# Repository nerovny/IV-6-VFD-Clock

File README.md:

# ИВ-6 VFD Digital Clock
+ _board: revision 1.0.0_
+ _firmware: version 0.1 Alpha_
## Overview
This is a basic 6-digit, 7-segment clock based on Soviet ИВ-6 vacuum fluorescent tubes, powered by a widely accessible STM32F103CBT6 microcontroller. 

+ No AI
+ No WiFi
+ USB-C powered

The core concept involves using a single 5V (USB-C) power source and converting the voltage to the 3.3V, 1.2V, and 30–35V levels required to operate the VFD tubes, microcontroller, and logic ICs. 
These circuits can be seen around the location of the rotary encoder on the right side of the board.

The circuit employs sequential updating of CD4511 BCD-to-7-segment latches and static control of the vacuum fluorescent tubes using TBD62783A eight-channel drivers. 
The static function of the VFD eliminates the flickering, extends the life of the lamps, but requires much more ICs.

The unused MCU pins and 5v, 3v3 power rails are accessible via the 2.54mm headers and can be used for an additional LEDs, buttons, logic circuitry etc.

## Hardware
The 110x54mm 4-layer board is tight, but definitely doable by hand with the good iron. The road is mastered by the one who walks it.
+ [Schematic PDF](hardware/schematic.pdf)
+ [Interactive BOM HTML](http://htmlpreview.github.io/?https://github.com/nerovny/IV-6-VFD-Clock/blob/main/hardware/bom/ibom.html)
+ [Board dimensions](hardware/VFD_IV6_dimensions.png)
+ [Fabrication files](hardware/Gerber/)

## Firmware
The latest binary is [HERE](https://github.com/nerovny/IV-6-VFD-Clock/releases)

Use the onboard SWD header and STM32CubeProgrammer to flash it.

The firmware made with VSCode + PlatformIO using some HAL drivers. Source code is provided: just clone the repo and open the project with PIO VSCode plugin.

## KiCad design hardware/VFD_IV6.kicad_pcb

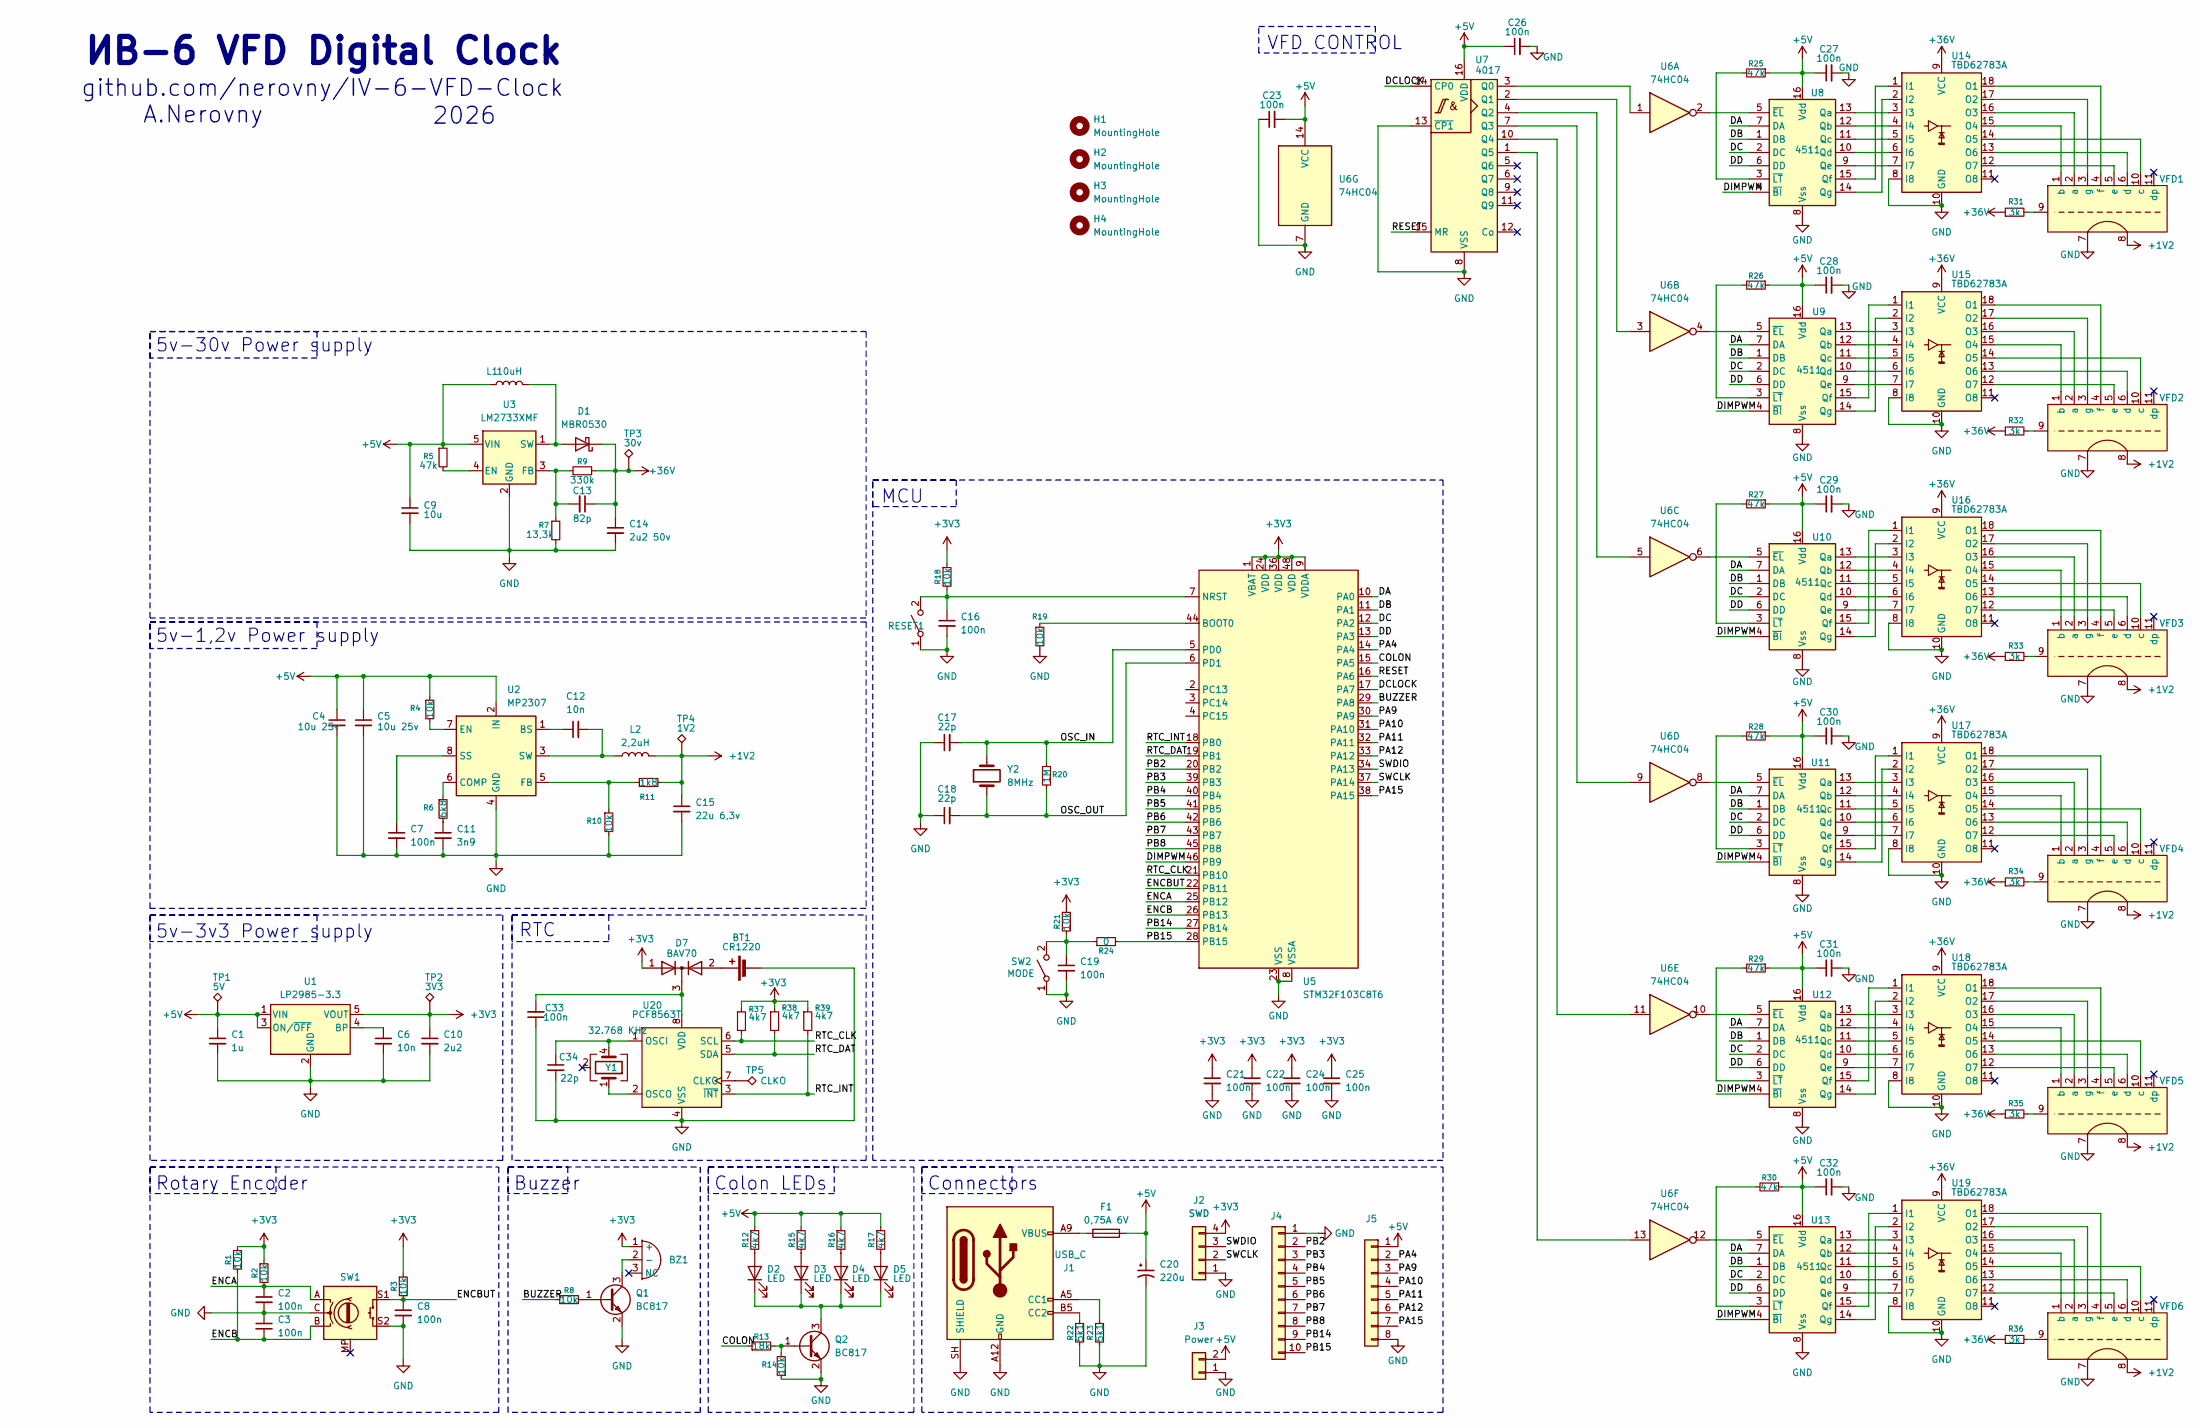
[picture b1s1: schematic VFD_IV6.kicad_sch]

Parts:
BT1: CR1220; RSPRO1220
BZ1: HCT5020
C1: 1u; C_0805_2012Metric
C2, C3, C7, C8, C16, C19, C21, C22, C24, C25, C33: 100n; C_0603_1608Metric
C4, C5: 10u 25v; C_0805_2012Metric
C6, C12: 10n; C_0603_1608Metric
C9: 10u; C_0805_2012Metric
C10: 2u2; C_0805_2012Metric
C11: 3n9; C_0603_1608Metric
C13: 82p; C_0603_1608Metric
C14: 2u2 50v; C_1210_3225Metric
C15: 22u 6,3v; C_1210_3225Metric
C17, C18: 22p; C_0603_1608Metric
C20: 220u; CP_EIA-7360-38_Kemet-E
C23, C26, C27, C28, C29, C30, C31, C32: 100n; C_0805_2012Metric
C34: 22p; C_0402_1005Metric
D1: MBR0530; D_SOD-123
D2, D3, D4, D5: LED; LED_0603_1608Metric
D7: BAV70; SOT-23
F1: 0,75A 6V; Fuse_1210_3225Metric
H1, H2, H3, H4: MountingHole; MountingHole_2.7mm_M2.5_DIN965_Pad
J1: USB_C; USB_C_Receptacle_HRO_TYPE-C-31-M-17
J2: SWD; PinHeader_1x04_P2.54mm_Vertical
J3: Power; JST_XH_B2B-XH-A_1x02_P2.50mm_Vertical
J4: Conn_01x10; PinHeader_1x10_P2.54mm_Vertical
J5: Conn_01x06; PinHeader_1x08_P2.54mm_Vertical
L1: 10uH; L_APV_APH0650
L2: 2,2uH; L_APV_APH0650
Q1, Q2: BC817; SOT-23
R1, R2, R3, R4, R8, R10, R14, R18, R19, R21: 10k; R_0603_1608Metric
R5, R25, R26, R27, R28, R29, R30: 47k; R_0603_1608Metric
R6: 6k8; R_0603_1608Metric
R7: 13,3k; R_0603_1608Metric
R9: 330k; R_0603_1608Metric
R11: 1k8; R_0603_1608Metric
R12, R15, R16, R17: 4k7; R_0603_1608Metric
R13: 18k; R_0603_1608Metric
R20: 1M; R_0603_1608Metric
R22, R23: 5k1; R_0603_1608Metric
R24: 0; R_0603_1608Metric
R31, R32, R33, R34, R35, R36: 3k; R_1206_3216Metric
R37, R38, R39: 4k7; R_0402_1005Metric
RESET1: SW_SPST; SW_SPST_CK_RS282G05A3
SW1: RotaryEncoder_Switch_MP; RotaryEncoder_Alps_EC12E-Switch_Vertical_H20mm
SW2: MODE; SW_Tactile_SPST_Angled_PTS645Vx39-2LFS
TP1: 5V; TestPoint_Pad_1.0x1.0mm
TP2: 3V3; TestPoint_Pad_1.0x1.0mm
TP3: 30v; TestPoint_Pad_1.0x1.0mm
TP4: 1V2; TestPoint_Pad_1.0x1.0mm
TP5: CLKO; TestPoint_Pad_1.0x1.0mm
U1: LP2985-3.3; SOT-23-5
U2: MP2307; SOIC-8_3.9x4.9mm_P1.27mm
U3: LM2733XMF; SOT-23-5
U5: STM32F103C8T6; LQFP-48_7x7mm_P0.5mm
U6: 74HC04; SOIC-14_3.9x8.7mm_P1.27mm
U7: 4017; SOIC-16_3.9x9.9mm_P1.27mm
U8, U9, U10, U11, U12, U13: 4511; SOP-16_4.4x10.4mm_P1.27mm
U14, U15, U16, U17, U18, U19: TBD62783A; SOIC-18W_7.5x11.6mm_P1.27mm
U20: PCF8563T; SOIC-8_3.9x4.9mm_P1.27mm
VFD1, VFD2, VFD3, VFD4, VFD5, VFD6: IV-6_Horizontal
Y1: 32.768 KHz; Crystal_SMD_SeikoEpson_MC306-4Pin_8.0x3.2mm
Y2: 8MHz; Crystal_SMD_5032-2Pin_5.0x3.2mm_HandSoldering

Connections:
+1V2: C15.1, L2.2, R11.2, TP4.1 (1_1), VFD1.8, VFD2.8, VFD3.8, VFD4.8, VFD5.8, VFD6.8
+3V3: BZ1.1 (+), C10.1, C21.1, C22.1, C24.1, C25.1, D7.1 (A), J2.4, R1.1, R2.1, R3.1, R18.1, R21.1, R37.1, R38.1, R39.1, TP2.1 (1_1), U1.5 (VOUT), U5.1 (VBAT), U5.9 (VDDA), U5.24 (VDD), U5.36 (VDD), U5.48 (VDD)
+5V: C1.1, C4.1, C5.1, C9.1, C20.1, C23.2, C26.1, C27.1, C28.1, C29.1, C30.1, C31.1, C32.1, F1.1, J3.2, J5.1, L1.1, R4.1, R5.1, R12.1, R15.1, R16.1, R17.1, R25.1, R26.1, R27.1, R28.1, R29.1, R30.1, TP1.1 (1_1), U1.1 (VIN), U1.3 (ON/~OFF), U2.2 (IN), U3.5 (VIN), U6.14 (VCC), U7.16 (VDD), U8.16 (Vdd), U9.16 (Vdd), U10.16 (Vdd), U11.16 (Vdd), U12.16 (Vdd), U13.16 (Vdd)
+36V: C13.1, C14.1, D1.1 (K), R9.2, R31.1, R32.1, R33.1, R34.1, R35.1, R36.1, TP3.1 (1_1), U14.9 (VCC), U15.9 (VCC), U16.9 (VCC), U17.9 (VCC), U18.9 (VCC), U19.9 (VCC)
/BUZZER: R8.1, U5.29 (PA8)
/COLON: R13.1, U5.15 (PA5)
/DA: U5.10 (PA0), U8.7 (DA), U9.7 (DA), U10.7 (DA), U11.7 (DA), U12.7 (DA), U13.7 (DA)
/DB: U5.11 (PA1), U8.1 (DB), U9.1 (DB), U10.1 (DB), U11.1 (DB), U12.1 (DB), U13.1 (DB)
/DC: U5.12 (PA2), U8.2 (DC), U9.2 (DC), U10.2 (DC), U11.2 (DC), U12.2 (DC), U13.2 (DC)
/DCLOCK: U5.17 (PA7), U7.14 (CP0); also elsewhere on the board
/DD: U5.13 (PA3), U8.6 (DD), U9.6 (DD), U10.6 (DD), U11.6 (DD), U12.6 (DD), U13.6 (DD)
/DIMPWM: U5.46 (PB9), U8.4 (~BI), U9.4 (~BI), U10.4 (~BI), U11.4 (~BI), U12.4 (~BI), U13.4 (~BI)
/ENCA: C2.1, R2.2, SW1.A, U5.25 (PB12)
/ENCB: C3.2, R1.2, SW1.B, U5.26 (PB13)
/ENCBUT: C8.1, R3.2, SW1.S1, U5.22 (PB11)
/OSC_IN: C17.2, R20.1, U5.5 (PD0), Y2.2
/OSC_OUT: C18.2, R20.2, U5.6 (PD1), Y2.1
/PA4: J5.2, U5.14 (PA4)
/PA9: J5.3, U5.30 (PA9)
/PA10: J5.4, U5.31 (PA10)
/PA11: J5.5, U5.32 (PA11)
/PA12: J5.6, U5.33 (PA12)
/PA15: J5.7, U5.38 (PA15)
/PB2: J4.2, U5.20 (PB2)
/PB3: J4.3, U5.39 (PB3)
/PB4: J4.4, U5.40 (PB4)
/PB5: J4.5, U5.41 (PB5)
/PB6: J4.6, U5.42 (PB6)
/PB7: J4.7, U5.43 (PB7)
/PB8: J4.8, U5.45 (PB8)
/PB14: J4.9, U5.27 (PB14)
/PB15: J4.10, R24.2, U5.28 (PB15)
/RESET: U5.16 (PA6), U7.15 (MR)
/RTC_CLK: R37.2, U5.21 (PB10), U20.6 (SCL)
/RTC_DAT: R38.2, U5.19 (PB1), U20.5 (SDA)
/RTC_INT: R39.2, U5.18 (PB0), U20.3 (~INT)
/SWCLK: J2.2, U5.37 (PA14)
/SWDIO: J2.3, U5.34 (PA13)
GND: BT1.2 (-), C1.2, C2.2, C3.1, C4.2, C5.2, C6.2, C7.2, C8.2, C9.2, C10.2, C11.2, C14.2, C15.2, C16.2, C17.1, C18.1, C19.2, C20.2, C21.2, C22.2, C23.1, C24.2, C25.2, C26.2, C27.2, C28.2, C29.2, C30.2, C31.2, C32.2, C33.1, C34.2, J1.A12 (GND), J1.B12 (GND), J1.SH (SHIELD), J2.1, J3.1, J4.1, J5.8, Q1.2 (E), Q2.2 (E), R7.2, R10.2, R14.1, R19.2, R22.2, R23.2, RESET1.1 (A), SW1.C, SW1.S2, SW2.1 (A), U1.2 (GND), U2.4 (GND), U3.2 (GND), U5.8 (VSSA), U5.23 (VSS), U5.35 (VSS), U5.47 (VSS), U6.7 (GND), U7.8 (VSS), U7.13 (~CP1), U8.8 (Vss), U9.8 (Vss), U10.8 (Vss), U11.8 (Vss), U12.8 (Vss), U13.8 (Vss), U14.8 (I8), U14.10 (GND), U15.8 (I8), U15.10 (GND), U16.8 (I8), U16.10 (GND), U17.8 (I8), U17.10 (GND), U18.8 (I8), U18.10 (GND), U19.8 (I8), U19.10 (GND), U20.4 (VSS), VFD1.7, VFD2.7, VFD3.7, VFD4.7, VFD5.7, VFD6.7; also elsewhere on the board
unnamed: BT1.1 (+), D7.2 (A)
unnamed: BZ1.2 (-), Q1.3 (C)
unnamed: C11.1, R6.2
unnamed: D1.2 (A), L1.2, U3.1 (SW)
unnamed: D2.2 (A), R12.2
unnamed: D2.1 (K), D3.1 (K), D4.1 (K), D5.1 (K), Q2.3 (C)
unnamed: D3.2 (A), R15.2
unnamed: D4.2 (A), R16.2
unnamed: D5.2 (A), R17.2
unnamed: C33.2, D7.3 (K), U20.8 (VDD)
unnamed: F1.2, J1.A9 (VBUS), J1.B9 (VBUS)
unnamed: J1.A5 (CC1), R23.1
unnamed: J1.B5 (CC2), R22.1
unnamed: Q1.1 (B), R8.2
unnamed: Q2.1 (B), R13.2, R14.2
unnamed: R31.2, VFD1.9
unnamed: R32.2, VFD2.9
unnamed: R33.2, VFD3.9
unnamed: R34.2, VFD4.9
unnamed: R35.2, VFD5.9
unnamed: R36.2, VFD6.9
unnamed: C16.1, R18.2, RESET1.2 (B), U5.7 (NRST)
unnamed: C19.1, R21.2, R24.1, SW2.2 (B)
unnamed: C6.1, U1.4 (BP)
unnamed: C12.1, U2.1 (BS)
unnamed: R6.1, U2.6 (COMP)
unnamed: R4.2, U2.7 (EN)
unnamed: R10.1, R11.1, U2.5 (FB)
unnamed: C7.1, U2.8 (SS)
unnamed: C12.2, L2.1, U2.3 (SW)
unnamed: R5.2, U3.4 (EN)
unnamed: C13.2, R7.1, R9.1, U3.3 (FB)
unnamed: R19.1, U5.44 (BOOT0)
unnamed: U6.1, U7.3 (Q0)
unnamed: U6.3, U7.2 (Q1)
unnamed: U6.5, U7.4 (Q2)
unnamed: U6.9, U7.7 (Q3)
unnamed: U6.11, U7.10 (Q4)
unnamed: U6.13, U7.1 (Q5)
unnamed: U6.2, U8.5 (~EL)
unnamed: R25.2, U8.3 (~LT)
unnamed: U6.4, U9.5 (~EL)
unnamed: R26.2, U9.3 (~LT)
unnamed: U10.13 (Qa), U16.3 (I3)
unnamed: U10.12 (Qb), U16.4 (I4)
unnamed: U10.11 (Qc), U16.5 (I5)
unnamed: U10.10 (Qd), U16.6 (I6)
unnamed: U10.9 (Qe), U16.7 (I7)
unnamed: U10.15 (Qf), U16.1 (I1)
unnamed: U10.14 (Qg), U16.2 (I2)
unnamed: U6.6, U10.5 (~EL)
unnamed: R27.2, U10.3 (~LT)
unnamed: U11.13 (Qa), U17.3 (I3)
unnamed: U11.12 (Qb), U17.4 (I4)
unnamed: U11.11 (Qc), U17.5 (I5)
unnamed: U11.10 (Qd), U17.6 (I6)
unnamed: U11.9 (Qe), U17.7 (I7)
unnamed: U11.15 (Qf), U17.1 (I1)
unnamed: U11.14 (Qg), U17.2 (I2)
unnamed: U6.8, U11.5 (~EL)
unnamed: R28.2, U11.3 (~LT)
unnamed: U12.13 (Qa), U18.3 (I3)
unnamed: U12.12 (Qb), U18.4 (I4)
unnamed: U12.11 (Qc), U18.5 (I5)
unnamed: U12.10 (Qd), U18.6 (I6)
unnamed: U12.9 (Qe), U18.7 (I7)
unnamed: U12.15 (Qf), U18.1 (I1)
unnamed: U12.14 (Qg), U18.2 (I2)
unnamed: U6.10, U12.5 (~EL)
unnamed: R29.2, U12.3 (~LT)
unnamed: U13.13 (Qa), U19.3 (I3)
unnamed: U13.12 (Qb), U19.4 (I4)
unnamed: U13.11 (Qc), U19.5 (I5)
unnamed: U13.10 (Qd), U19.6 (I6)
unnamed: U13.9 (Qe), U19.7 (I7)
unnamed: U13.15 (Qf), U19.1 (I1)
unnamed: U13.14 (Qg), U19.2 (I2)
unnamed: U6.12, U13.5 (~EL)
unnamed: R30.2, U13.3 (~LT)
unnamed: U8.15 (Qf), U14.1 (I1)
unnamed: U8.14 (Qg), U14.2 (I2)
unnamed: U8.13 (Qa), U14.3 (I3)
unnamed: U8.12 (Qb), U14.4 (I4)
unnamed: U8.11 (Qc), U14.5 (I5)
unnamed: U8.10 (Qd), U14.6 (I6)
unnamed: U8.9 (Qe), U14.7 (I7)
unnamed: U14.18 (O1), VFD1.4 (f)
unnamed: U14.17 (O2), VFD1.3 (g)
unnamed: U14.16 (O3), VFD1.2 (a)
unnamed: U14.15 (O4), VFD1.1 (b)
unnamed: U14.14 (O5), VFD1.10 (c)
unnamed: U14.13 (O6), VFD1.6 (d)
unnamed: U14.12 (O7), VFD1.5 (e)
unnamed: U9.15 (Qf), U15.1 (I1)
unnamed: U9.14 (Qg), U15.2 (I2)
unnamed: U9.13 (Qa), U15.3 (I3)
unnamed: U9.12 (Qb), U15.4 (I4)
unnamed: U9.11 (Qc), U15.5 (I5)
unnamed: U9.10 (Qd), U15.6 (I6)
unnamed: U9.9 (Qe), U15.7 (I7)
unnamed: U15.18 (O1), VFD2.4 (f)
unnamed: U15.17 (O2), VFD2.3 (g)
unnamed: U15.16 (O3), VFD2.2 (a)
unnamed: U15.15 (O4), VFD2.1 (b)
unnamed: U15.14 (O5), VFD2.10 (c)
unnamed: U15.13 (O6), VFD2.6 (d)
unnamed: U15.12 (O7), VFD2.5 (e)
unnamed: U16.18 (O1), VFD3.4 (f)
unnamed: U16.17 (O2), VFD3.3 (g)
unnamed: U16.16 (O3), VFD3.2 (a)
unnamed: U16.15 (O4), VFD3.1 (b)
unnamed: U16.14 (O5), VFD3.10 (c)
unnamed: U16.13 (O6), VFD3.6 (d)
unnamed: U16.12 (O7), VFD3.5 (e)
unnamed: U17.18 (O1), VFD4.4 (f)
unnamed: U17.17 (O2), VFD4.3 (g)
unnamed: U17.16 (O3), VFD4.2 (a)
unnamed: U17.15 (O4), VFD4.1 (b)
unnamed: U17.14 (O5), VFD4.10 (c)
unnamed: U17.13 (O6), VFD4.6 (d)
unnamed: U17.12 (O7), VFD4.5 (e)
unnamed: U18.18 (O1), VFD5.4 (f)
unnamed: U18.17 (O2), VFD5.3 (g)
unnamed: U18.16 (O3), VFD5.2 (a)
unnamed: U18.15 (O4), VFD5.1 (b)
unnamed: U18.14 (O5), VFD5.10 (c)
unnamed: U18.13 (O6), VFD5.6 (d)
unnamed: U18.12 (O7), VFD5.5 (e)
unnamed: U19.18 (O1), VFD6.4 (f)
unnamed: U19.17 (O2), VFD6.3 (g)
unnamed: U19.16 (O3), VFD6.2 (a)
unnamed: U19.15 (O4), VFD6.1 (b)
unnamed: U19.14 (O5), VFD6.10 (c)
unnamed: U19.13 (O6), VFD6.6 (d)
unnamed: U19.12 (O7), VFD6.5 (e)
unnamed: TP5.1 (1_1), U20.7 (CLKO)
unnamed: C34.1, U20.1 (OSCI), Y1.4
unnamed: U20.2 (OSCO), Y1.1

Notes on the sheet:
5v-3v3 Power supply
5v-1,2v Power supply
VFD CONTROL
MCU
github.com/nerovny/IV-6-VFD-Clock
ИВ-6 VFD Digital Clock
RTC
Colon LEDs
Buzzer
A.Nerovny
2026
Connectors
5v-30v Power supply
Rotary Encoder

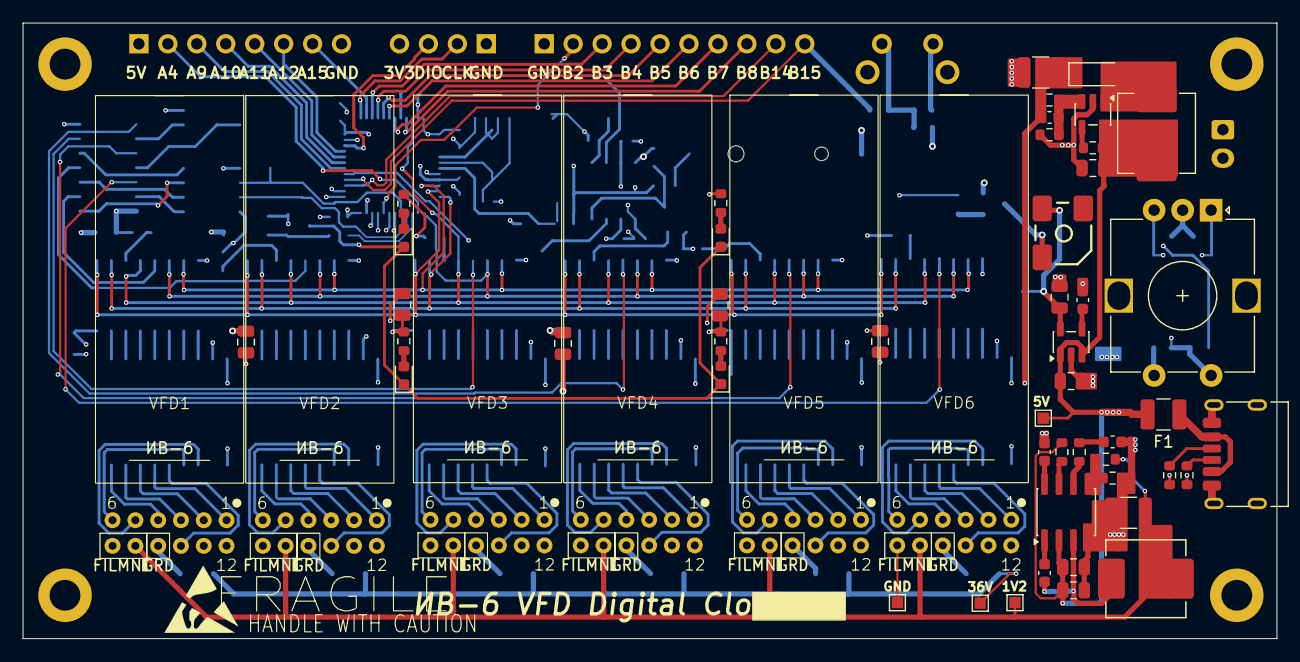
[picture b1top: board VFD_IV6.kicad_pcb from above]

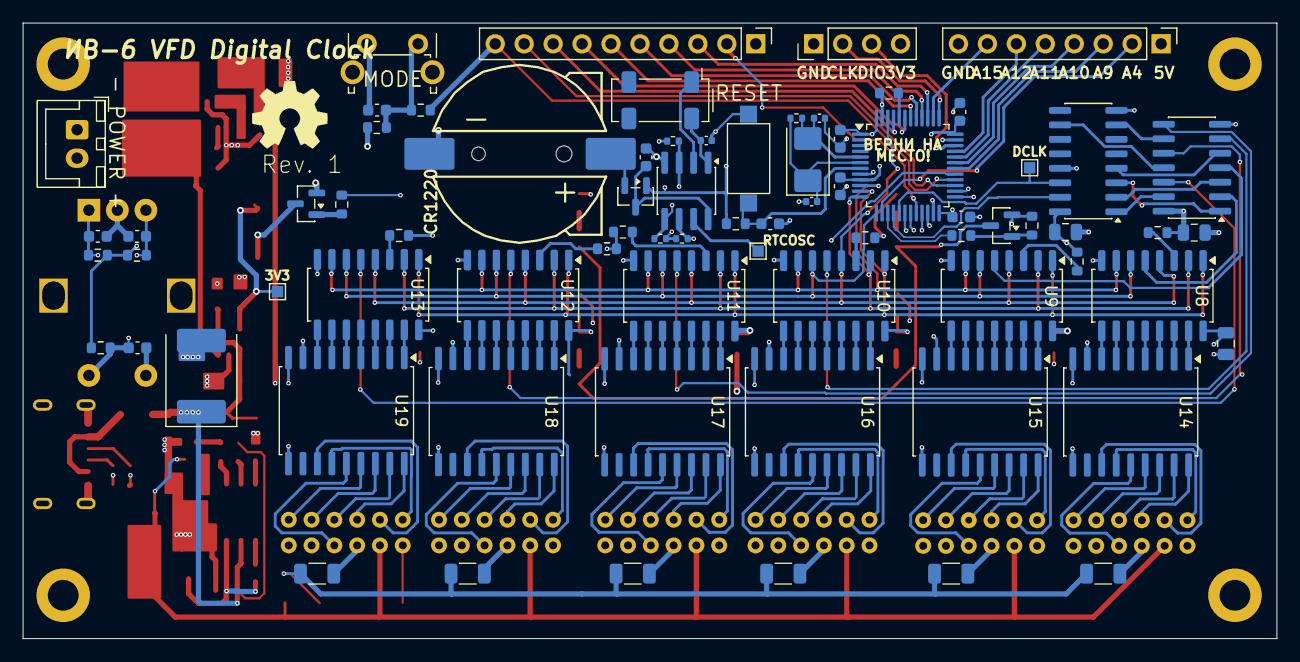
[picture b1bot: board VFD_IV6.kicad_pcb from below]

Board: 4 copper layers, 110.0 x 54.0 mm, 132 parts (74 on the bottom side), 177 nets.

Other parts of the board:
TP4#2, TP4#3: 30v; TestPoint_Pad_1.0x1.0mm

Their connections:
/DCLOCK: TP4#3.1 (1_1); also elsewhere on the board
GND: TP4#2.1 (1_1); also elsewhere on the board

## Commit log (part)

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2026-06-15 Fixed BCDZero and BCDReset functions
2026-06-18 Added hardware Kicad project files
2026-06-18 Source files and headers added
2026-06-18 Updated the output functions
2026-06-18 RTC module changes
2026-06-19 Used DS1302 external clock module
2026-06-19 Updated schematic pdf
2026-06-21 Higher speed, better look
2026-06-21 Updated .gitignore
